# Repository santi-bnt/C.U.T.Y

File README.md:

# C.U.T.Y — Companion Unit That Yaps

Compañero de escritorio expresivo. La voz desarrollada en Windows y el menú/cara subidos desde la Raspberry conviven en este repositorio.

## Cinco áreas principales

```text
C.U.T.Y/
├── raspberry/
│   ├── src/cuty/      Voz, conversación y proveedores
│   ├── touchscreen/   Menú táctil, cara demo, Wi-Fi y servicio
│   ├── tests/
│   ├── scripts/       Preparación de Windows/Raspberry
│   └── systemd/       Plantilla futura del servicio de voz
├── stm32/             Firmware futuro: servos, IMU, PID, UART y seguridad
├── hardware/
│   ├── cad/           SolidWorks y exportaciones STEP/STL/GLB
│   └── electronics/   KiCad, esquemas y datasheets
├── web/               Portafolio EN/ES y visor 3D; dashboard conectado futuro
└── docs/              Arquitectura, planes y protocol/
```

Las entradas de voz, pantalla e instalación están dentro de `raspberry/`. El GLB fuente está en `hardware/cad/glb/` y la copia que usa el visor en `web/public/models/`. La raíz conserva documentación, licencia y configuración del repositorio; ya no contiene lanzadores de compatibilidad. Las carpetas ocultas del entorno no son módulos del robot.

## Estado

- Voz: push-to-talk, Gemini predeterminado, OpenAI opcional, búsqueda web, contexto de sesión, idioma según la pregunta y frases de espera en español.
- Pantalla: menú Terminal/Internet/C.U.T.Y, Wi-Fi y **cara animada**: ojos que parpadean y miran alrededor, toque para parpadear y pulsación continua de cinco segundos para volver al menú.
- Cara conectada: con cámara, los ojos **siguen a la persona**; las expresiones de la conversación aparecen en la cara y la **boca se mueve con la voz** (enlace UDP local entre la voz y la pantalla). Ver [cara](docs/face.md).
- Conversación desde el menú: toca C.U.T.Y para recibir un saludo y hablar sin ENTER; di «quiero salir» para volver al inicio. Usa Gemini, el entorno existente y una clave local en `.env`. Ver [configuración](raspberry/touchscreen/README.md#conversación-desde-el-menú).
- Electrónica: [carrier PCB v1.1](hardware/electronics/kicad/cuty_carrier/README.md) para Raspberry Pi 5 y STM32F401 Black Pill, con KiCad, Gerbers, BOM y esquemático. Fabricación, montaje y validación eléctrica pendientes.
- Firmware STM32F401, control de servos, dashboard y mecánica siguen pendientes de implementación.

Raspberry posee IA, voz, pantalla, visión y comportamiento. STM32 poseerá PWM, movimiento, IMU, PID y seguridad: recibirá objetivos de alto nivel, no PWM continuo. Los ejemplos UART siguen siendo propuestas.

## Voz en Windows

Desde la raíz, entra al proyecto de Raspberry y utiliza su entorno:

```powershell
cd raspberry
.\.venv\Scripts\python.exe -m cuty
.\.venv\Scripts\python.exe -m pytest -q -p no:cacheprovider
```

Preparación del entorno desde la raíz del repositorio: `./raspberry/scripts/dev_setup.ps1`.
Consulta [la guía de voz](raspberry/README.md). Configura `raspberry/.env`; el lector aún admite un `.env` en la raíz para instalaciones anteriores. No subir claves.

## Pantalla en Raspberry

Consulta [las instrucciones de pantalla](raspberry/touchscreen/README.md). Requiere Linux, framebuffer RGB565, ADS7846, calibración local y dependencias de sistema. Las dependencias Python de pantalla están separadas en `raspberry/touchscreen/requirements.txt`; no instalar evdev en Windows.

Entrada manual: `sudo python3 raspberry/touchscreen/cuty_launcher.py` desde la raíz. Instalación explícita: `bash raspberry/touchscreen/install.sh`, después de probar la pantalla. El servicio actual ya apunta a `raspberry/touchscreen/cuty_launcher.py`; esta limpieza no cambia sus rutas ni la calibración del hardware.

## Web

Consulta [ejecución y despliegue](web/README.md). Desde `web/`, usa `npm ci` y `npm run dev` para abrir el portafolio con el robot negro y su LCD integrado. La web es frontend y funciona sin una Raspberry encendida.

[Arquitectura](docs/architecture.md) · [Roadmap](docs/roadmap.md) · [Protocolo](docs/protocol/protocol.md) · [Movimientos e integración](docs/reorganization.md)

[Mapa de conexiones por bloques (HTML)](docs/conexiones.html) · [Señales (SVG)](docs/assets/conexiones-senales.svg) · [Alimentación (SVG)](docs/assets/conexiones-alimentacion.svg)

Las pruebas locales no certifican la pantalla física ni el arranque de su servicio tras reiniciar la Raspberry

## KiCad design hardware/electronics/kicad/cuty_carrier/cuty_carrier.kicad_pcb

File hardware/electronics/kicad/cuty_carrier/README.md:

# C.U.T.Y — Placa base (carrier) v1.1

[Diagrama por bloques interactivo (HTML)](../../../../docs/conexiones.html) · [Señales (SVG)](../../../../docs/assets/conexiones-senales.svg) · [Alimentación (SVG)](../../../../docs/assets/conexiones-alimentacion.svg)

PCB de 2 capas que reemplaza la protoboard y los cables Dupont. Interconecta
la Raspberry Pi 5, la STM32F401 Black Pill, la pantalla Display-G de 3.5 in,
el ReSpeaker 2-Mics Pi HAT V2.0 y los cinco MG996R, y distribuye la energía
de la LiPo 3S. Todos los módulos van enchufados (cables planos con llave,
zócalos y tiras de pines), así que se pueden quitar o reemplazar.

| | |
| --- | --- |
| Tamaño | 100 × 92 mm, esquinas redondeadas, 4 barrenos M3 |
| Capas | 2 (F.Cu / B.Cu), FR-4 1.6 mm |
| Componentes | 100 % de agujero pasante (THT): pedido documentado con ensamble JLCPCB (`fab/jlcpcb/`); paquete PCBA de PCBWay conservado como alternativa (`fab/pcba/`) |
| Pista / espacio mínimo | 0.30 mm / 0.25 mm (señales); 2.5–3.0 mm en potencia |
| Taladro mínimo | 0.40 mm (vías 0.8/0.4); 2 ranuras de 0.6 mm (patas del XT60) |
| DRC guardado | 0 entradas de severidad error, 0 pads sin conectar y 50 advertencias de serigrafía (`drc_report.txt`) |
| Gerbers | 0 cortos, 0 abiertos, taladro y máscara en cada pad (`scripts/verify_gerbers.py`) |

El pedido documentado en [`fab/jlcpcb/`](fab/jlcpcb/LEEME_JLCPCB.md) registra
37 componentes THT soldados por JLCPCB. Los portafusibles F1/F2, sus fusibles
y el puente JP1 se colocan a mano. La recepción, integración y validación
eléctrica deben verificarse por separado. Los resultados DRC y Gerber son los
reportes guardados en el proyecto; integrar estos archivos no equivale a
repetir las verificaciones con KiCad.

## Alternativa de ensamble: PCBWay

1. Comprime el contenido de **`fab/gerbers/`** como `CUTY_carrier_PCBWay_gerbers.zip`
   y súbelo en *PCB Instant Quote → Quick-order PCB*. El ZIP no está versionado;
   los archivos Gerber y los taladros sí están incluidos.
   PCBWay detecta el tamaño (100 × 92 mm) y las 2 capas.
2. Opciones:
   - Material FR-4, TG130 · Espesor 1.6 mm · Capas 2
   - Pista/espacio mínimos 6/6 mil · Taladro mínimo 0.3 mm (cualquier valor estándar sirve)
   - Acabado HASL lead free · Máscara verde · Serigrafía blanca
   - **Cobre: 1 oz** basta para uso normal. **Si los 5 servos van a forzar a la vez, pide 2 oz.**
     Las pistas de batería son de 3 mm y el bus de 6 V va en ambas capas.
   - Cantidad: 5 (el mínimo)
3. **Ensamblada (recomendado):** sigue [`fab/pcba/LEEME_PCBA.md`](fab/pcba/LEEME_PCBA.md). Ahí están el BOM con
   números de parte del fabricante, el archivo de centroid, el dibujo de ensamble con la polaridad
   y el texto para las notas del pedido. PCBWay compra y suelda las 39 piezas; tú solo pones la
   Black Pill y los fusibles.
4. **Para soldarla tú:** la lista de compras está en `fab/cuty_carrier_BOM.csv`.

## Qué hay en la placa

**Energía** (bornes en el borde superior e izquierdo):

```
LiPo 3S ─ J1 XT60 ─ J2 interruptor general ─┬─ F1 10 A ─ J3 interruptor servos ─ J4 → buck → J5 6 V ─ C1/C2 ─ servos
                                            └─ F2 5 A ─ J6 → regulador 5.1 V / 5 A ─ USB-C ─ Raspberry Pi 5
```

- **J2 y J3** son bornes para interruptores de panel externos de al menos 10 A.
- **Tierras.** PGND (potencia: batería, buck, servos) y GND (lógica: Pi,
  STM32, audio, pantalla) son dos planos separados. Solo se unen en **NT1**,
  junto a la entrada de batería. Así la corriente de los servos no regresa
  por la tierra del audio ni de la lógica.
- **Rieles.** La Pi recibe su energía por USB-C desde el regulador, como pide
  la especificación. La pantalla y el ReSpeaker toman 5 V y 3.3 V de los
  pines de la Pi, como cuando estaban montados sobre ella. La 3.3 V y la 5 V
  nunca se tocan.
- **STM32.** Toma 5 V de la Pi a través de **JP1** (jumper) y **D1** (1N5819).
  D1 evita que el USB de la Black Pill alimente de regreso a la Pi. Quita el
  jumper si quieres alimentar la STM32 solo por USB mientras la programas.
  La 3.3 V de la Black Pill (`+3V3_BP`) es independiente de la 3.3 V de la Pi.
- **LEDs.** BAT (rojo), 6V (azul) y 5V Pi (verde).
- **Tornillos.** Alrededor de los 4 barrenos M3 no hay cobre, para que un separador
  metálico no pueda unir GND y PGND a través del chasis.

**Señales**

| Origen | Destino | Nota |
| --- | --- | --- |
| Pi pin 8 (TX) | PA3 USART2_RX | Cruzado |
| Pi pin 10 (RX) | PA2 USART2_TX | |
| PB6 / PB7 / PB8 / PB9 | Servos 1–4 (J7–J10) | TIM4 CH1–CH4, 220 Ω en serie |
| PA8 | Servo 5 (J11) | TIM1 CH1, 220 Ω en serie |
| PA1 | Divisor de batería | V<sub>bat</sub> = V<sub>ADC</sub> × 122 / 22 (12.6 V → 2.27 V). PA0 queda libre porque tiene el botón KEY de la Black Pill |
| PB10 / PB3 | J15 I2C2 (SCL/SDA) | Para la IMU futura, con pull-ups de 4.7 kΩ |
| J12 ↔ J13 | Pantalla (por cable) | Pines 1, 2, 4, 6, 11, 17–26 y GND, numeración física idéntica a la Pi |
| J12 ↔ J14 | ReSpeaker | Pines 1–7, 12, 17, 35, 37, 38, 40 y GND. Quedan libres 8, 10, 11, 19, 23, 32, 33 y los demás |

Cada servo usa el orden estándar **– + S** (marrón, rojo, naranja). El
negativo queda hacia el borde de la placa.

## Antes de soldar y conectar (revisar sí o sí)

1. **Black Pill.** Va con los componentes hacia arriba y el USB-C hacia el borde
   derecho. Arriba queda la fila PB12…3V3 (PB12 junto al USB) y abajo la fila
   VBAT…5V (5V junto al USB). El footprint sigue la numeración y la geometría
   del modelo STEP oficial de WeAct (filas a 15.215 mm). Los nombres de los pines
   están impresos entre los zócalos para que compruebes antes de insertar.
   Si a tu módulo le soldaron el header SWD hacia abajo, la placa tiene
   barrenos libres para esos 4 pines.
2. **Ajusta el buck a 6.0 V con el multímetro antes de conectarlo a J5.**
3. **Polaridad.** Revisa la polaridad del XT60: el pad de arriba es **+**. La
   PCB lleva el XT60 **macho**; la batería debe tener XT60 hembra.
4. **Cables planos.** Ambos van rectos, de pin 1 a pin 1 (hilo rojo al pin 1);
   la flecha ▽ marca el pin 1 y el box header no deja conectarlos al revés.
   - **J12 → Raspberry Pi 5:** cable IDC de 40 vías hembra–hembra.
   - **J13 → pantalla:** la pantalla va en la cabeza, que se mueve, así que se
     conecta por cable: extensión GPIO de 26 vías **hembra–macho** (o un cable
     IDC hembra–hembra más una tira 2×13 macho–macho). Insértala en la pantalla
     igual que en una Pi.
5. **ReSpeaker.** Se inserta directo en J14 como sobre la Pi, con el pin 1 a la
   derecha (cuadro). Su placa (65 × 30 mm) queda sobre el área de pistas, donde solo
   hay componentes bajos, y termina 2.5 mm antes del conector de la Pi.
6. **Raspberry Pi 5.** En `config.txt` activa la UART de GPIO14/15
   (`dtparam=uart0=on`). Si el regulador de 5.1 V no negocia USB-PD, agrega
   `usb_max_current_enable=1` para que la Pi no limite sus puertos USB a 600 mA.
   Valida el enlace UART antes de dar el diseño por definitivo.
7. **Batería.** La placa solo protege con fusibles. La LiPo sigue necesitando
   una alarma o BMS de sobredescarga y un cargador balanceador 3S.

## Archivos

| Archivo | Qué es |
| --- | --- |
| `cuty_carrier.kicad_pro/.kicad_sch/.kicad_pcb` | Proyecto KiCad 7, abre en KiCad 7, 8 y 9 |
| `CUTY.kicad_sym`, `CUTY.pretty/` | Símbolo y footprint propios de la Black Pill (tablas de bibliotecas incluidas) |
| `fab/gerbers/` | Gerbers RS-274X y taladros Excellon (PTH y NPTH separados) |
| `fab/cuty_carrier_BOM.csv` | Lista de materiales para soldar a mano |
| `fab/pcba/` | Pedido ensamblado en PCBWay: BOM y centroid (xlsx/csv), dibujo de ensamble (PDF/SVG), instrucciones |
| `fab/cuty_carrier_esquematico.pdf` | Esquemático |
| `fab/preview/` | Render de los Gerbers (como saldrá fabricada) |
| `drc_report.txt` | Reporte DRC |
| `scripts/` | Generadores: el diseño completo se reconstruye desde `netlist.py` |

### Regenerar el diseño

Requisitos: KiCad 7+, Python con `sexpdata`, Java 21 y el `.jar` de Freerouting.

```sh
cd scripts
python3 netlist.py                      # verifica la tabla de conexiones
python3 gen_lib.py && python3 gen_sch.py
/usr/bin/python3 gen_pcb.py             # Python de KiCad (pcbnew)
/usr/bin/python3 route.py freerouting.jar 60   # o "reuse" para reusar _route/board.ses
/usr/bin/python3 verify_pcb.py          # paridad pad por pad con netlist.py
/usr/bin/python3 verify_spec.py         # la PCB contra las conexiones especificadas
/usr/bin/python3 verify_gerbers.py      # cortos/abiertos, taladros y mascara en los Gerbers reales
/usr/bin/python3 gen_pcba.py           # BOM y centroid para PCBWay (fab/pcba/)
/usr/bin/python3 gen_asm_svg.py && python3 gen_asm_pdf.py   # dibujo de ensamble con polaridad
```

`netlist.py` es la única fuente de verdad: si cambias una conexión ahí,
el esquemático y la PCB salen iguales.

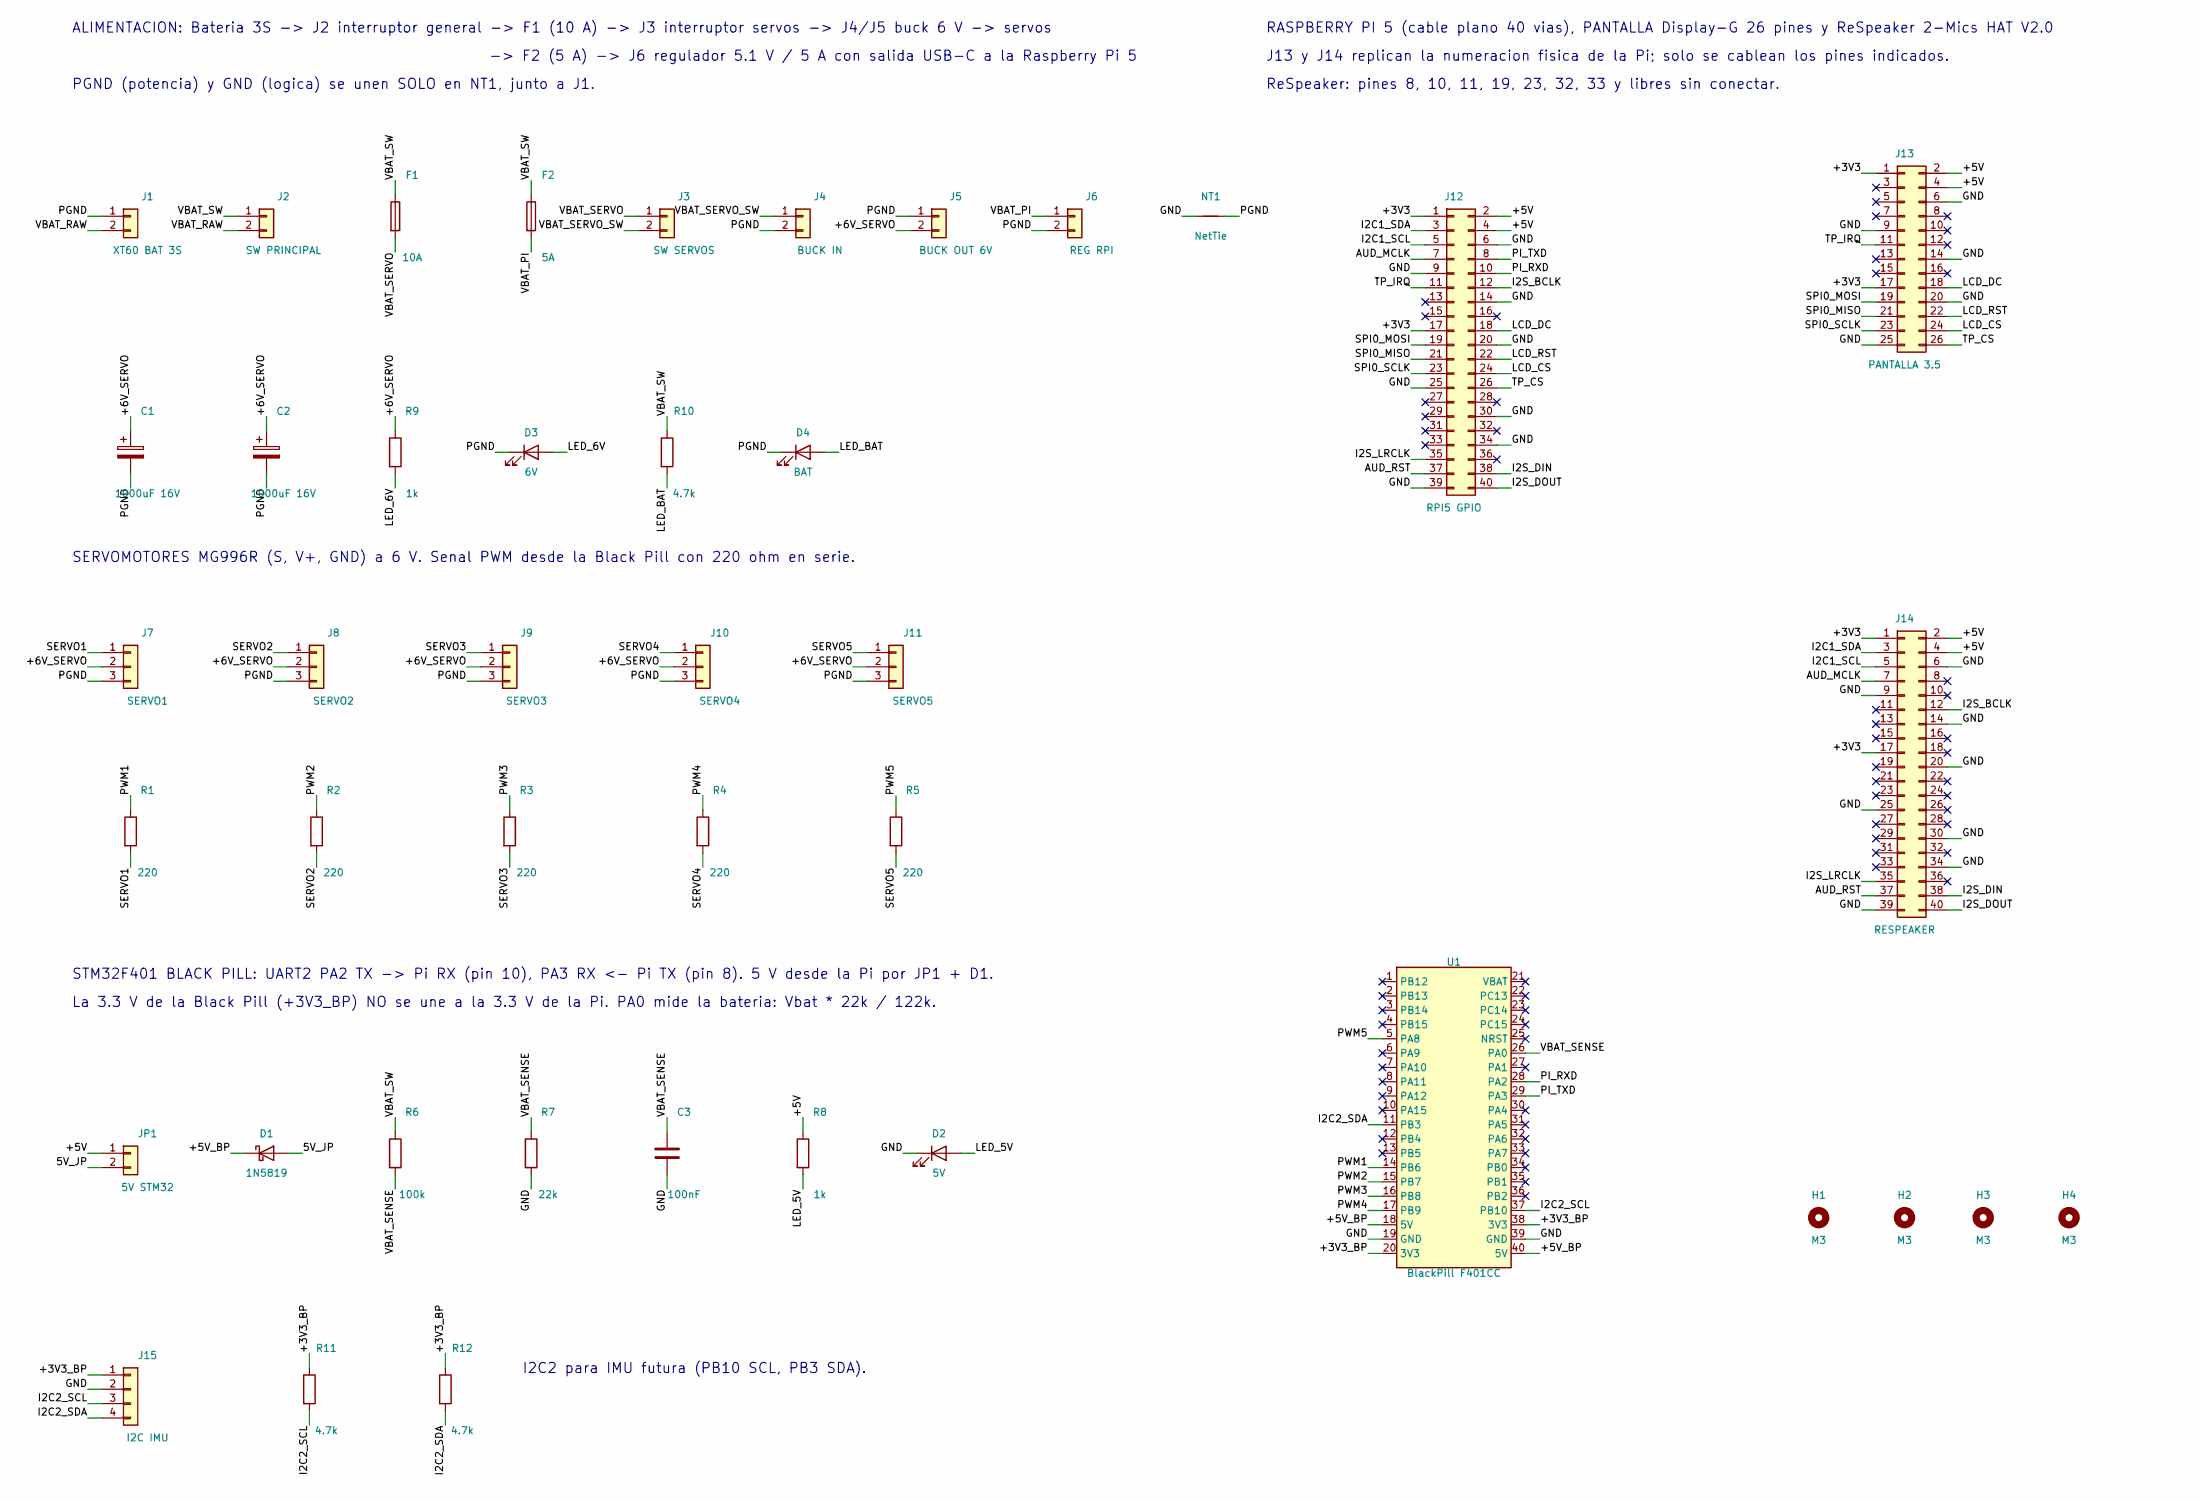
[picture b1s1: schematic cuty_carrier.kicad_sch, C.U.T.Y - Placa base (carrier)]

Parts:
C1, C2: 1000uF 16V; CP_Radial_D10.0mm_P5.00mm
C3: 100nF; C_Disc_D5.0mm_W2.5mm_P5.00mm
D1: 1N5819; D_DO-41_SOD81_P10.16mm_Horizontal
D2: 5V; LED_D3.0mm
D3: 6V; LED_D3.0mm
D4: BAT; LED_D3.0mm
F1: 10A; Fuseholder_Blade_Mini_Keystone_3568
F2: 5A; Fuseholder_Blade_Mini_Keystone_3568
H1, H2, H3, H4: M3; MountingHole_3.2mm_M3
J1: XT60 BAT 3S; AMASS_XT60PW-M_1x02_P7.20mm_Horizontal
J2: SW PRINCIPAL; TerminalBlock_Phoenix_MKDS-1,5-2-5.08_1x02_P5.08mm_Horizont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
J3: SW SERVOS; TerminalBlock_Phoenix_MKDS-1,5-2-5.08_1x02_P5.08mm_Horizont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
J4: BUCK IN; TerminalBlock_Phoenix_MKDS-1,5-2-5.08_1x02_P5.08mm_Horizont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
J5: BUCK OUT 6V; TerminalBlock_Phoenix_MKDS-1,5-2-5.08_1x02_P5.08mm_Horizont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
J6: REG RPI; TerminalBlock_Phoenix_MKDS-1,5-2-5.08_1x02_P5.08mm_Horizont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
J7: SERVO1; PinHeader_1x03_P2.54mm_Vertical
J8: SERVO2; PinHeader_1x03_P2.54mm_Vertical
J9: SERVO3; PinHeader_1x03_P2.54mm_Vertical
J10: SERVO4; PinHeader_1x03_P2.54mm_Vertical
J11: SERVO5; PinHeader_1x03_P2.54mm_Vertical
J12: RPI5 GPIO; IDC-Header_2x20_P2.54mm_Vertical
J13: PANTALLA 3.5; PinHeader_2x13_P2.54mm_Vertical
J14: RESPEAKER; PinHeader_2x20_P2.54mm_Vertical
J15: I2C IMU; PinHeader_1x04_P2.54mm_Vertical
JP1: 5V STM32; PinHeader_1x02_P2.54mm_Vertical
NT1: NetTie; NetTie-2_THT_Pad1.0mm
R1, R2, R3, R4, R5: 220; R_Axial_DIN0207_L6.3mm_D2.5mm_P7.62mm_Horizontal
R6: 100k; R_Axial_DIN0207_L6.3mm_D2.5mm_P7.62mm_Horizontal
R7: 22k; R_Axial_DIN0207_L6.3mm_D2.5mm_P7.62mm_Horizontal
R8, R9: 1k; R_Axial_DIN0207_L6.3mm_D2.5mm_P7.62mm_Horizontal
R10, R11, R12: 4.7k; R_Axial_DIN0207_L6.3mm_D2.5mm_P7.62mm_Horizontal
U1: BlackPill F401CC; WeAct_BlackPill_Socket

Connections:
5V_JP: D1.2 (A), JP1.2
+3V3: J12.1, J12.17, J13.1, J13.17, J14.1, J14.17
+3V3_BP: J15.1, R11.1, R12.1, U1.20 (3V3), U1.38 (3V3)
+5V: J12.2, J12.4, J13.2, J13.4, J14.2, J14.4, JP1.1, R8.1
+5V_BP: D1.1 (K), U1.18 (5V), U1.40 (5V)
+6V_SERVO: C1.1, C2.1, J5.2, J7.2, J8.2, J9.2, J10.2, J11.2, R9.1
AUD_MCLK: J12.7, J14.7
AUD_RST: J12.37, J14.37
GND: C3.2, D2.1 (K), J12.6, J12.9, J12.14, J12.20, J12.25, J12.30, J12.34, J12.39, J13.6, J13.9, J13.14, J13.20, J13.25, J14.6, J14.9, J14.14, J14.20, J14.25, J14.30, J14.34, J14.39, J15.2, NT1.1, R7.2, U1.19 (GND), U1.39 (GND)
I2C1_SCL: J12.5, J14.5
I2C1_SDA: J12.3, J14.3
I2C2_SCL: J15.3, R11.2, U1.37 (PB10)
I2C2_SDA: J15.4, R12.2, U1.11 (PB3)
I2S_BCLK: J12.12, J14.12
I2S_DIN: J12.38, J14.38
I2S_DOUT: J12.40, J14.40
I2S_LRCLK: J12.35, J14.35
LCD_CS: J12.24, J13.24
LCD_DC: J12.18, J13.18
LCD_RST: J12.22, J13.22
LED_5V: D2.2 (A), R8.2
LED_6V: D3.2 (A), R9.2
LED_BAT: D4.2 (A), R10.2
PGND: C1.2, C2.2, D3.1 (K), D4.1 (K), J1.1, J4.2, J5.1, J6.2, J7.3, J8.3, J9.3, J10.3, J11.3, NT1.2
PI_RXD: J12.10, U1.28 (PA2)
PI_TXD: J12.8, U1.29 (PA3)
PWM1: R1.1, U1.14 (PB6)
PWM2: R2.1, U1.15 (PB7)
PWM3: R3.1, U1.16 (PB8)
PWM4: R4.1, U1.17 (PB9)
PWM5: R5.1, U1.5 (PA8)
SERVO1: J7.1, R1.2
SERVO2: J8.1, R2.2
SERVO3: J9.1, R3.2
SERVO4: J10.1, R4.2
SERVO5: J11.1, R5.2
SPI0_MISO: J12.21, J13.21
SPI0_MOSI: J12.19, J13.19
SPI0_SCLK: J12.23, J13.23
TP_CS: J12.26, J13.26
TP_IRQ: J12.11, J13.11
VBAT_PI: F2.2, J6.1
VBAT_RAW: J1.2, J2.2
VBAT_SENSE: C3.1, R6.2, R7.1, U1.26 (PA0), U1.27 (PA1)
VBAT_SERVO: F1.2, J3.1
VBAT_SERVO_SW: J3.2, J4.1
VBAT_SW: F1.1, F2.1, J2.1, R6.1, R10.1

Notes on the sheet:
ALIMENTACION: Bateria 3S -> J2 interruptor general -> F1 (10 A) -> J3 interruptor servos -> J4/J5 buck 6 V -> servos
-> F2 (5 A) -> J6 regulador 5.1 V / 5 A con salida USB-C a la Raspberry Pi 5
PGND (potencia) y GND (logica) se unen SOLO en NT1, junto a J1.
SERVOMOTORES MG996R (S, V+, GND) a 6 V. Senal PWM desde la Black Pill con 220 ohm en serie.
RASPBERRY PI 5 (cable plano 40 vias), PANTALLA Display-G 26 pines y ReSpeaker 2-Mics HAT V2.0
J13 y J14 replican la numeracion fisica de la Pi; solo se cablean los pines indicados.
ReSpeaker: pines 8, 10, 11, 19, 23, 32, 33 y libres sin conectar.
STM32F401 BLACK PILL: UART2 PA2 TX -> Pi RX (pin 10), PA3 RX <- Pi TX (pin 8). 5 V desde la Pi por JP1 + D1.
La 3.3 V de la Black Pill (+3V3_BP) NO se une a la 3.3 V de la Pi. PA0 mide la bateria: Vbat * 22k / 122k.
I2C2 para IMU futura (PB10 SCL, PB3 SDA).

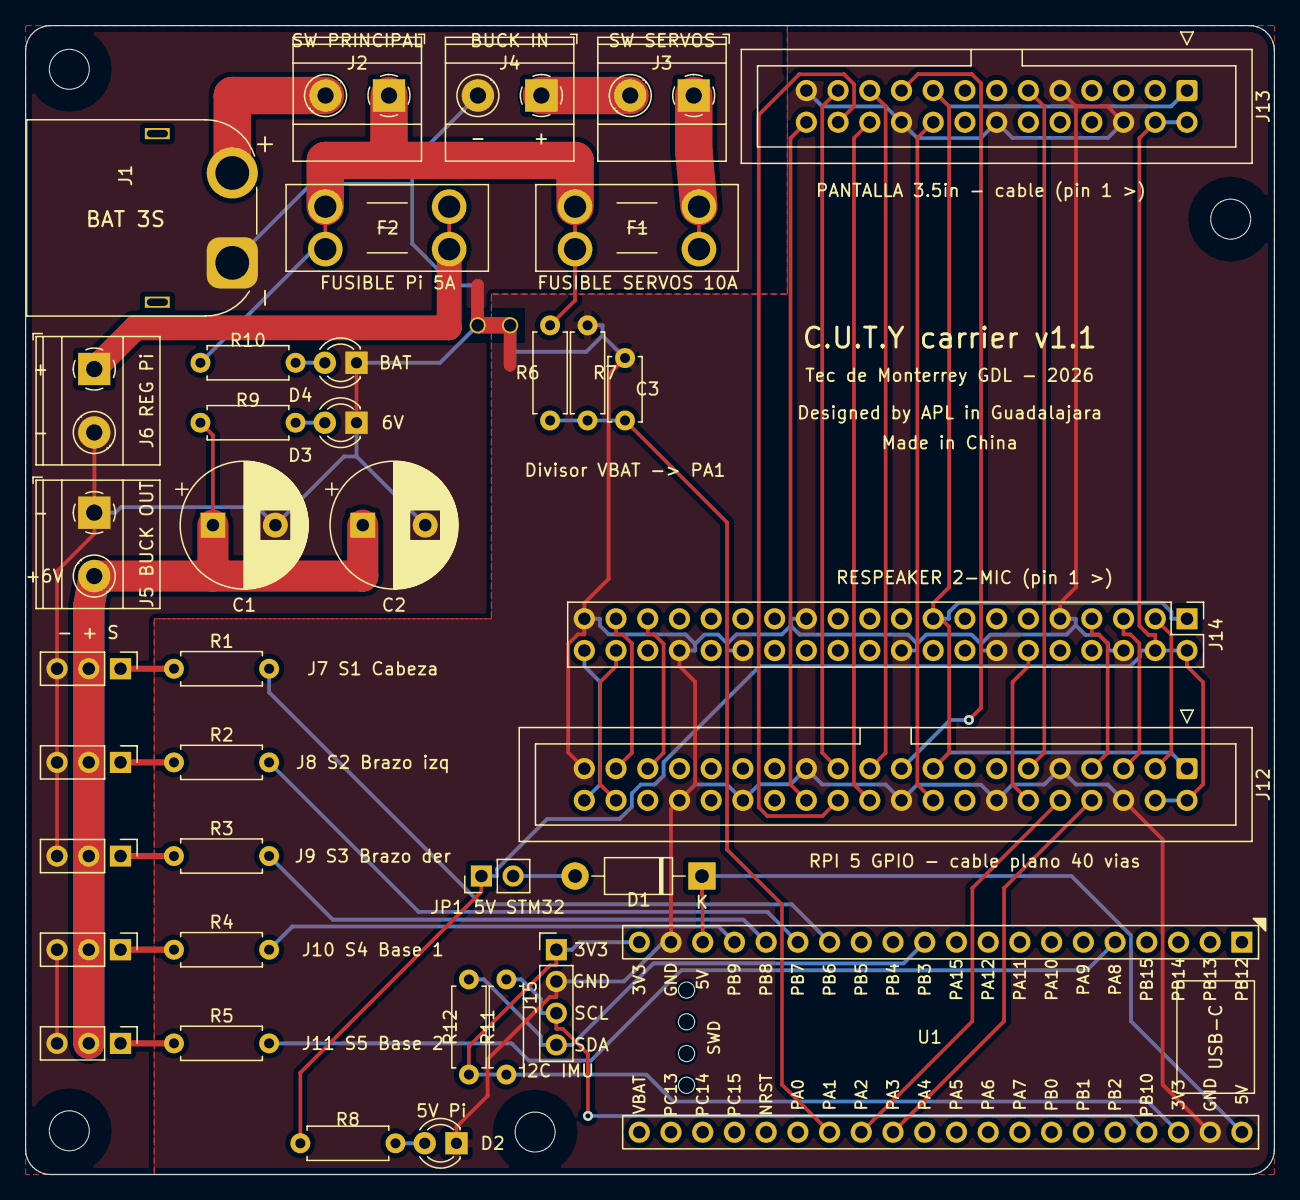
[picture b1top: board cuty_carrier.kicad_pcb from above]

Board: 2 copper layers, 100.0 x 92.0 mm, 43 parts (0 on the bottom side), 47 nets.

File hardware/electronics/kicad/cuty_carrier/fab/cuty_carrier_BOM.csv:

Referencias,Cantidad,Valor,Footprint,Comprar,Nota
J1,1,XT60 BAT 3S,AMASS_XT60PW-M_1x02_P7.20mm_Horizontal,AMASS XT60PW-M,Bateria LiPo 3S
J2,1,SW PRINCIPAL,"TerminalBlock_Phoenix_MKDS-1,5-2-5.08_1x02_P5.08mm_Horizontal","Phoenix MKDS 1,5/2-5,08",A interruptor general (>=10 A)
F1,1,10A,Fuseholder_Blade_Mini_Keystone_3568,Keystone 3568 + fusible mini 10 A,Fusible servos (mini blade 10 A)
F2,1,5A,Fuseholder_Blade_Mini_Keystone_3568,Keystone 3568 + fusible mini 5 A,Fusible Raspberry (mini blade 5 A)
J3,1,SW SERVOS,"TerminalBlock_Phoenix_MKDS-1,5-2-5.08_1x02_P5.08mm_Horizontal","Phoenix MKDS 1,5/2-5,08",A interruptor de servos
J4,1,BUCK IN,"TerminalBlock_Phoenix_MKDS-1,5-2-5.08_1x02_P5.08mm_Horizontal","Phoenix MKDS 1,5/2-5,08",Entrada del buck de servos
J5,1,BUCK OUT 6V,"TerminalBlock_Phoenix_MKDS-1,5-2-5.08_1x02_P5.08mm_Horizontal","Phoenix MKDS 1,5/2-5,08",Salida del buck ajustado a 6 V
J6,1,REG RPI,"TerminalBlock_Phoenix_MKDS-1,5-2-5.08_1x02_P5.08mm_Horizontal","Phoenix MKDS 1,5/2-5,08",Entrada del regulador 5.1 V / 5 A (USB-C a Pi 5)
C1 C2,2,1000uF 16V,CP_Radial_D10.0mm_P5.00mm,Electrolitico 1000 uF 16 V low-ESR D10 P5,
R9 R8,2,1k,R_Axial_DIN0207_L6.3mm_D2.5mm_P7.62mm_Horizontal,Resistencia 1/4 W,
D3,1,6V,LED_D3.0mm,LED 3 mm azul,
R10 R11 R12,3,4.7k,R_Axial_DIN0207_L6.3mm_D2.5mm_P7.62mm_Horizontal,Resistencia 1/4 W,
D4,1,BAT,LED_D3.0mm,LED 3 mm rojo,
R1 R2 R3 R4 R5,5,220,R_Axial_DIN0207_L6.3mm_D2.5mm_P7.62mm_Horizontal,Resistencia 1/4 W,
J7,1,SERVO1,PinHeader_1x03_P2.54mm_Vertical,Tira de pines 1x3 2.54 mm,MG996R Cabeza (S + -)
J8,1,SERVO2,PinHeader_1x03_P2.54mm_Vertical,Tira de pines 1x3 2.54 mm,MG996R Brazo izq (S + -)
J9,1,SERVO3,PinHeader_1x03_P2.54mm_Vertical,Tira de pines 1x3 2.54 mm,MG996R Brazo der (S + -)
J10,1,SERVO4,PinHeader_1x03_P2.54mm_Vertical,Tira de pines 1x3 2.54 mm,MG996R Base 1 (S + -)
J11,1,SERVO5,PinHeader_1x03_P2.54mm_Vertical,Tira de pines 1x3 2.54 mm,MG996R Base 2 (S + -)
J12,1,RPI5 GPIO,IDC-Header_2x20_P2.54mm_Vertical,Box header 2x20 2.54 mm,Cable plano 40 vias a la Raspberry Pi 5
J13,1,PANTALLA 3.5,PinHeader_2x13_P2.54mm_Vertical,Tira de pines 2x13 2.54 mm,Display-G 26 pines (waveshare35a)
J14,1,RESPEAKER,PinHeader_2x20_P2.54mm_Vertical,Tira de pines 2x20 2.54 mm,ReSpeaker 2-Mics Pi HAT V2.0
U1,1,BlackPill F401CC,WeAct_BlackPill_Socket,2x zocalo hembra 1x20 2.54 mm,WeAct Black Pill STM32F401CCU6
JP1,1,5V STM32,PinHeader_1x02_P2.54mm_Vertical,Tira 1x2 + jumper,Puente: 5 V de la Pi a la Black Pill
D1,1,1N5819,D_DO-41_SOD81_P10.16mm_Horizontal,1N5819,
R6,1,100k,R_Axial_DIN0207_L6.3mm_D2.5mm_P7.62mm_Horizontal,Resistencia 1/4 W 1%,
R7,1,22k,R_Axial_DIN0207_L6.3mm_D2.5mm_P7.62mm_Horizontal,Resistencia 1/4 W 1%,
C3,1,100nF,C_Disc_D5.0mm_W2.5mm_P5.00mm,Ceramico 100 nF 50 V,
D2,1,5V,LED_D3.0mm,LED 3 mm verde,
J15,1,I2C IMU,PinHeader_1x04_P2.54mm_Vertical,Tira de pines 1x4 2.54 mm,IMU futura en I2C2 de la STM32
-,2,Fusible mini blade,-,Fusible automotriz mini 10 A + 5 A,Para F1 (servos) y F2 (Pi)
-,1,Cable plano 40 vias,-,Cable IDC 2x20 hembra-hembra 10-15 cm,J12 a la Raspberry Pi 5
-,1,Jumper,-,Jumper 2.54 mm,JP1
-,4,Tornillo M3,-,Separador M3 10 mm + tornillo,H1-H4
